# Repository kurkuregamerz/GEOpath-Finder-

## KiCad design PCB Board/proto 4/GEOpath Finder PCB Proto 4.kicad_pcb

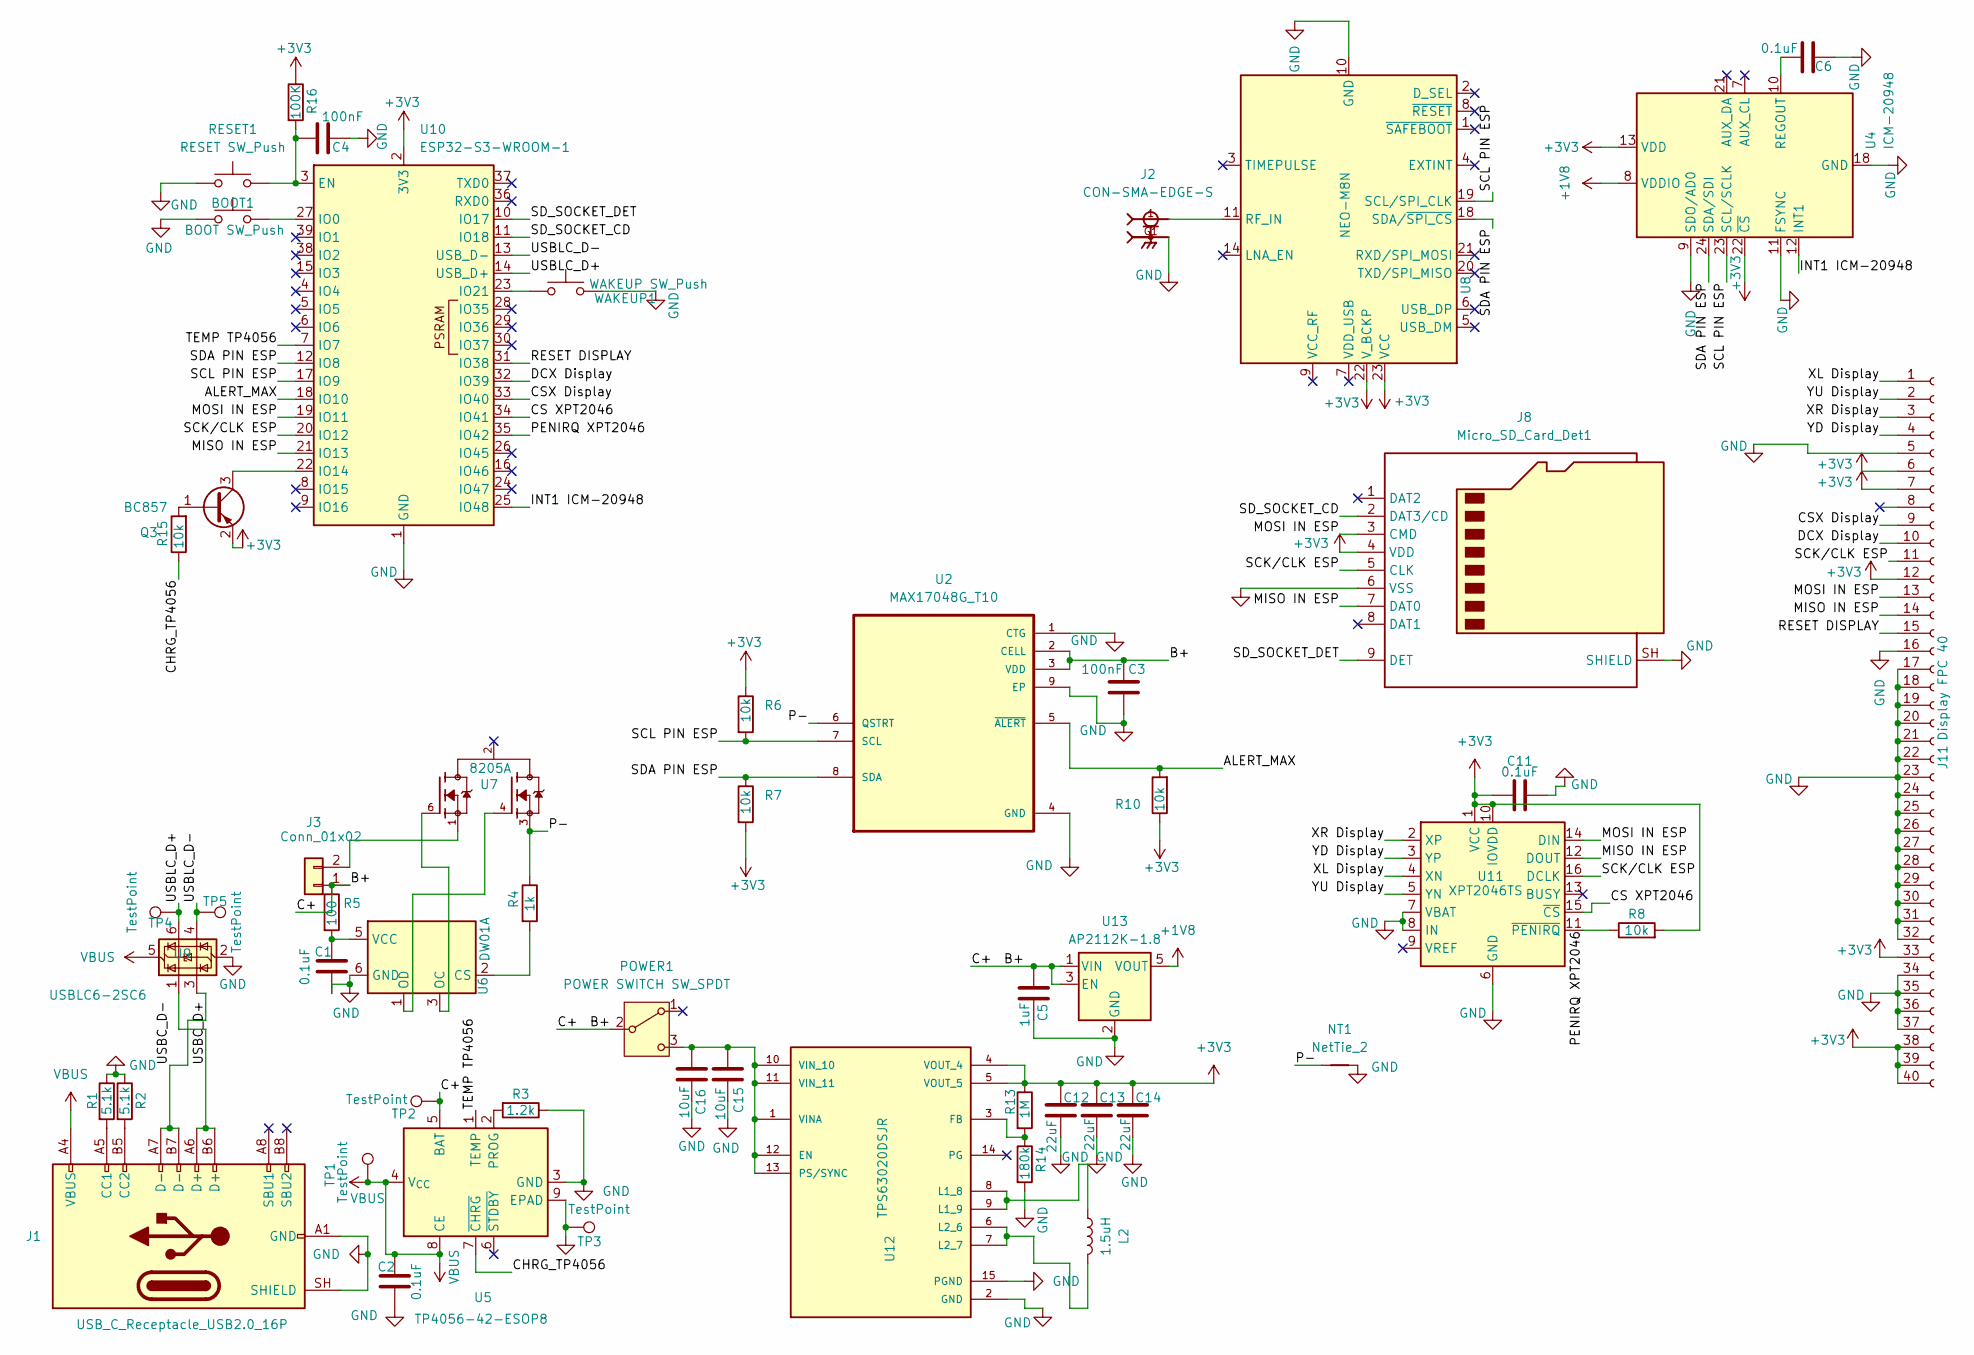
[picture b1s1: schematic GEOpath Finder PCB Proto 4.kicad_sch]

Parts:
BOOT1: BOOT SW_Push; SW_PUSH_6mm
C1, C2, C6, C11: 0.1uF; C_0201_0603Metric
C3, C4: 100nF; C_0201_0603Metric
C5: 1uF; C_0201_0603Metric
C12, C13, C14: 22uF; C_1206_3216Metric
C15, C16: 10uF; C_0603_1608Metric
J1: USB_C_Receptacle_USB2.0_16P; USB_C_Receptacle_GCT_USB4085
J2: CON-SMA-EDGE-S; RFSOLUTIONS_CON-SMA-EDGE-S; PARTREV 1
J3: Conn_01x02; JST_EH_S2B-EH_1x02_P2.50mm_Horizontal
J8: Micro_SD_Card_Det1; microSD_HC_Hirose_DM3AT-SF-PEJM5
J11: Display FPC 40; Amphenol_F32Q-1A7x1-11040_1x40-1MP_P0.5mm_Horizontal
L2: 1.5uH; L_0201_0603Metric
NT1: NetTie_2; NetTie-2_SMD_Pad0.5mm
POWER1: POWER SWITCH SW_SPDT; SW_Slide_SPDT_Angled_CK_OS102011MA1Q
Q3: BC857; SOT-23
R1, R2: 5.1k; R_0201_0603Metric
R3: 1.2k; R_0201_0603Metric
R4: 1k; R_0201_0603Metric
R5: 100; R_0201_0603Metric
R6, R7, R8, R10, R15: 10k; R_0201_0603Metric
R13: 1M; R_1206_3216Metric
R14: 180k; R_0201_0603Metric
R16: 100K; R_0201_0603Metric
RESET1: RESET SW_Push; SW_PUSH_6mm
TP1, TP2, TP3, TP4, TP5: TestPoint; TestPoint_THTPad_D1.0mm_Drill0.5mm
U2: MAX17048G_T10; SON50P200X200X80-9N; MPN MAX17048G+T10
U4: ICM-20948; InvenSense_QFN-24_3x3mm_P0.4mm
U5: TP4056-42-ESOP8; SOIC-8-1EP_3.9x4.9mm_P1.27mm_EP2.41x3.3mm_ThermalVias
U6: DW01A; SOT-23-6
U7: 8205A; SOT95P285X140-6N; PARTREV NA
U8: NEO-M8N; ublox_NEO
U9: USBLC6-2SC6; SOT-23-6
U10: ESP32-S3-WROOM-1
U11: XPT2046TS; TSSOP-16_4.4x5mm_P0.65mm
U12: TPS63020DSJR; IC_TPS63020DSJR; MPN TPS63020DSJR
U13: AP2112K-1.8; SOT-23-5
WAKEUP1: WAKEUP SW_Push; SW_Push_1P1T-MP_NO_Horizontal_Alps_SKRTLAE010

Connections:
+1V8: U4.8 (VDDIO), U13.5 (VOUT)
+3V3: C11.1, C12.1, C13.1, C14.1, J8.4 (VDD), J11.6, J11.7, J11.12, J11.33, J11.38, J11.39, J11.40, Q3.2 (E), R6.1, R7.2, R8.2, R10.1, R13.1, R16.1, U4.13 (VDD), U4.22 (~CS), U8.22 (V_BCKP), U8.23 (VCC), U10.2 (3V3), U11.1 (VCC), U11.10 (IOVDD), U12.4 (VOUT_4), U12.5 (VOUT_5)
/ALERT_MAX: R10.2, U2.5 (~ALERT), U10.18 (IO10)
/B+: C3.1, C5.1, J3.1, POWER1.2 (B), R5.1, TP2.1 (1_1), U2.2 (CELL), U2.3 (VDD), U5.5 (BAT), U13.1 (VIN), U13.3 (EN)
/CHRG_TP4056: R15.1, U5.7 (~CHRG)
/CS XPT2046: U10.34 (IO41), U11.15 (~CS)
/CSX Display: J11.9, U10.33 (IO40)
/DCX Display: J11.10, U10.32 (IO39)
/INT1 ICM-20948: U4.12 (INT1), U10.25 (IO48)
/MISO IN ESP: J8.7 (DAT0), J11.14, U10.21 (IO13), U11.12 (DOUT)
/MOSI IN ESP: J8.3 (CMD), J11.13, U10.19 (IO11), U11.14 (DIN)
/P-: NT1.1, R4.1, U2.6 (QSTRT), U7.3
/PENIRQ XPT2046: R8.1, U10.35 (IO42), U11.11 (~PENIRQ)
/RESET DISPLAY: J11.15, U10.31 (IO38)
/SCK/CLK ESP: J8.5 (CLK), J11.11, U10.20 (IO12), U11.16 (DCLK)
/SCL PIN ESP: R6.2, U2.7 (SCL), U4.23 (SCL/SCLK), U8.19 (SCL/SPI_CLK), U10.17 (IO9)
/SDA PIN ESP: R7.1, U2.8 (SDA), U4.24 (SDA/SDI), U8.18 (SDA/~SPI_CS), U10.12 (IO8)
/SD_SOCKET_CD: J8.2 (DAT3/CD), U10.11 (IO18)
/SD_SOCKET_DET: J8.9 (DET), U10.10 (IO17)
/TEMP TP4056: U5.1 (TEMP), U10.7 (IO7)
/USBC_D+: J1.A6 (D+), J1.B6 (D+), U9.1 (I/O1)
/USBC_D-: J1.A7 (D-), J1.B7 (D-), U9.3 (I/O2)
/USBLC_D+: TP4.1 (1_1), U9.6 (I/O1), U10.14 (USB_D+)
/USBLC_D-: TP5.1 (1_1), U9.4 (I/O2), U10.13 (USB_D-)
/XL Display: J11.1, U11.4 (XN)
/XR Display: J11.3, U11.2 (XP)
/YD Display: J11.4, U11.3 (YP)
/YU Display: J11.2, U11.5 (YN)
GND: BOOT1.1, C1.2, C2.2, C3.2, C4.2, C5.2, C6.2, C11.2, C12.2, C13.2, C14.2, C15.2, C16.2, J1.A1 (GND), J1.A12 (GND), J1.B1 (GND), J1.B12 (GND), J1.SH (SHIELD), J2.G1, J2.G2, J2.G3, J2.G4, J8.6 (VSS), J8.SH (SHIELD), J11.5, J11.16, J11.17, J11.18, J11.19, J11.20, J11.21, J11.22, J11.23, J11.24, J11.25, J11.26, J11.27, J11.28, J11.29, J11.30, J11.31, J11.32, J11.34, J11.35, J11.36, J11.37, NT1.2, R1.1, R2.1, R3.1, R14.2, RESET1.1, TP3.1 (1_1), U2.1 (CTG), U2.4 (GND), U2.9 (EP), U4.9 (SDO/AD0), U4.11 (FSYNC), U4.18 (GND), U4.20 (GND), U5.3 (GND), U5.9 (EPAD), U6.6 (GND), U8.10 (GND), U8.12 (GND), U8.13 (GND), U8.24 (GND), U9.2 (GND), U10.1 (GND), U10.40 (GND), U10.41 (GND), U11.6 (GND), U11.7 (VBAT), U11.8 (IN), U12.2 (GND), U12.15 (PGND), U13.2 (GND), WAKEUP1.2
unnamed: J1.A5 (CC1), R1.2
unnamed: J1.B5 (CC2), R2.2
unnamed: J3.2, U7.1
unnamed: C15.1, C16.1, POWER1.3 (C), U12.1 (VINA), U12.10 (VIN_10), U12.11 (VIN_11), U12.12 (EN), U12.13 (PS/SYNC)
unnamed: Q3.1 (B), R15.2
unnamed: Q3.3 (C), U10.22 (IO14)
unnamed: C6.1, U4.10 (REGOUT)
unnamed: R3.2, U5.2 (PROG)
unnamed: R4.2, U6.2 (CS)
unnamed: U6.3 (OC), U7.6
unnamed: U6.1 (OD), U7.4
unnamed: C1.1, R5.2, U6.5 (VCC)
unnamed: J2.1, U8.11 (RF_IN)
unnamed: C4.1, R16.2, RESET1.2, U10.3 (EN)
unnamed: BOOT1.2, U10.27 (IO0)
unnamed: U10.23 (IO21), WAKEUP1.1
unnamed: R13.2, R14.1, U12.3 (FB)
unnamed: L2.1, U12.8 (L1_8), U12.9 (L1_9)
unnamed: L2.2, U12.6 (L2_6), U12.7 (L2_7)
VBUS: C2.1, J1.A4 (VBUS), J1.A9 (VBUS), J1.B4 (VBUS), J1.B9 (VBUS), TP1.1 (1_1), U5.4 (V_{CC}), U5.8 (CE), U9.5 (VBUS)

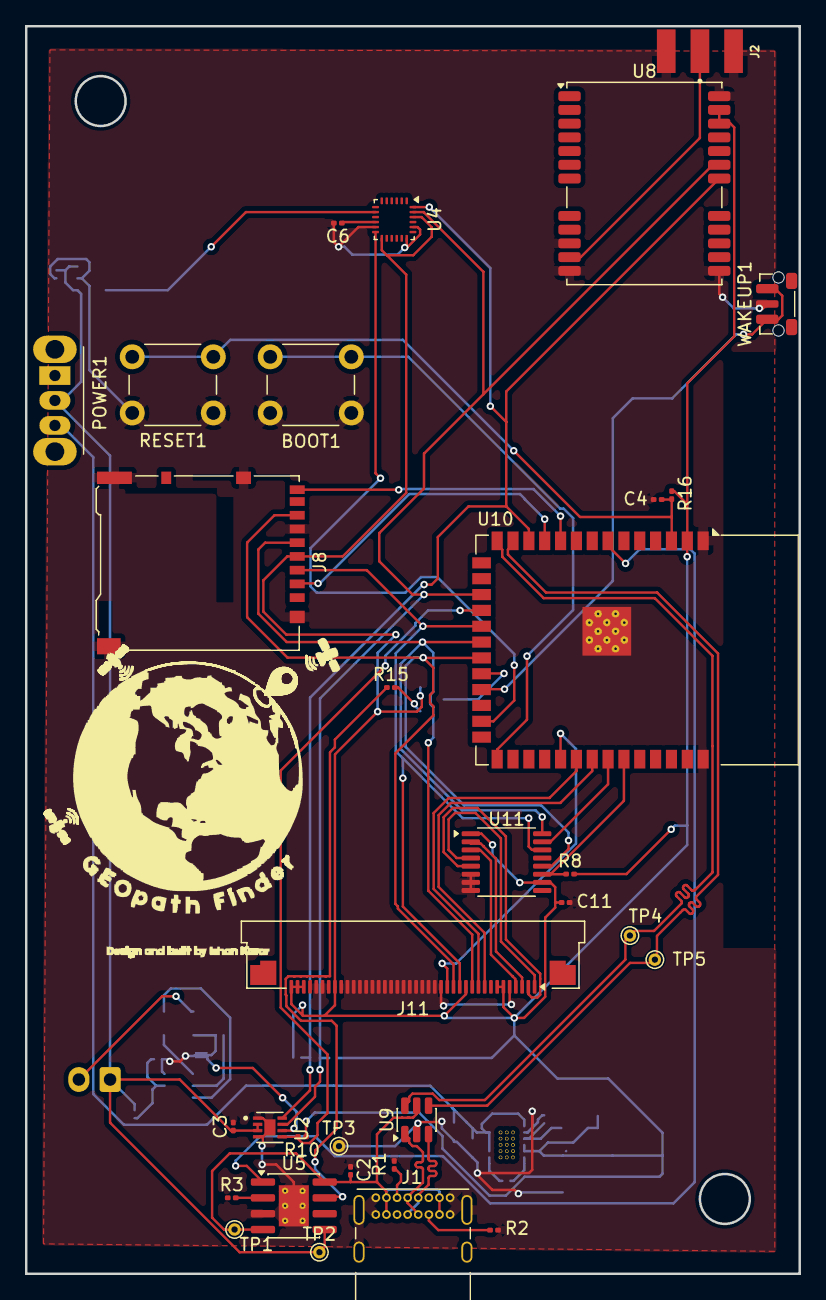
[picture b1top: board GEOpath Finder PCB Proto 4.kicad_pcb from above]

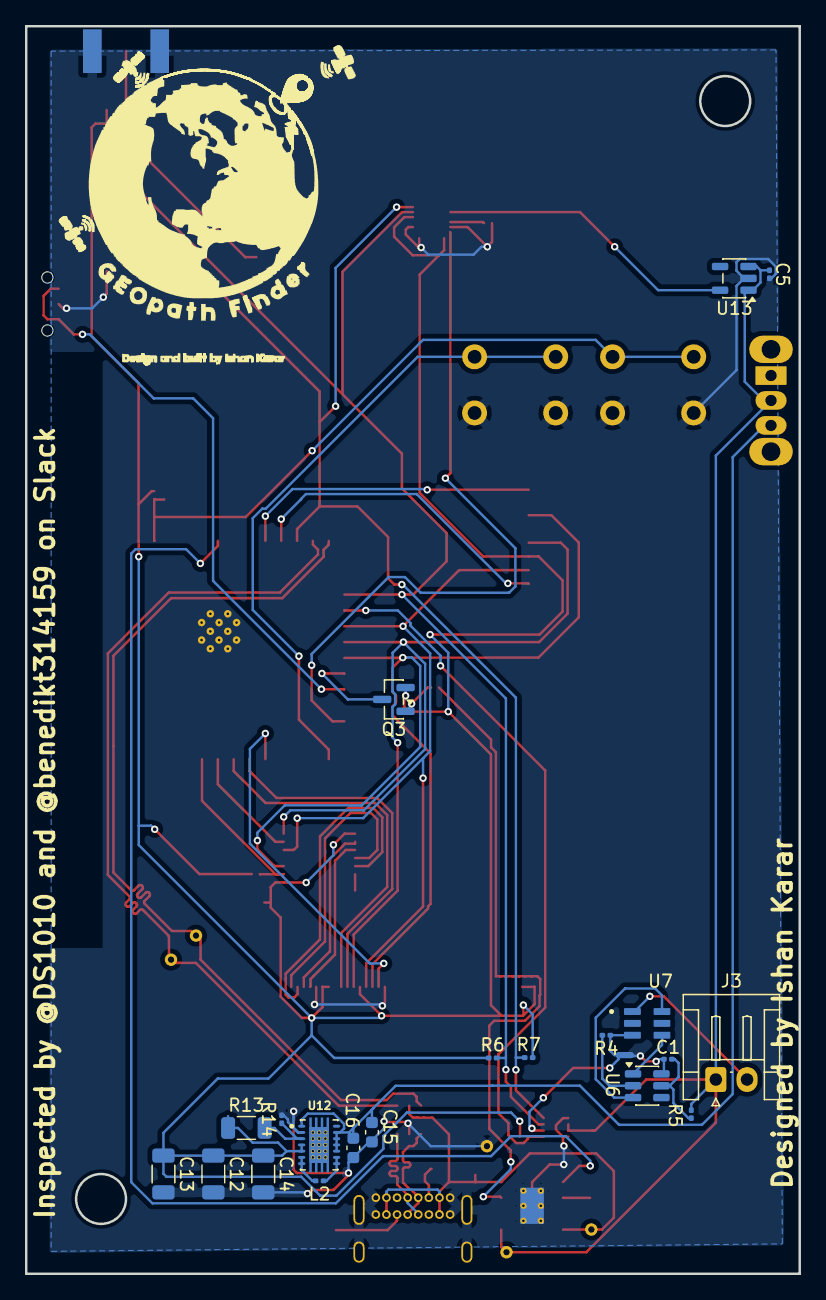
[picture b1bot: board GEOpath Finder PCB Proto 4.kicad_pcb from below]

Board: 2 copper layers, 62.0 x 100.0 mm, 53 parts (21 on the bottom side), 49 nets.

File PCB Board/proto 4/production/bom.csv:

Designator,Footprint,Quantity,Value,LCSC Part #
BOOT1,SW_PUSH_6mm,1,BOOT SW_Push,
"C1, C11, C2, C6",0201,4,0.1uF,
"C12, C13, C14",1206,3,22uF,
"C15, C16",0603,2,10uF,
"C3, C4",0201,2,100nF,
C5,0201,1,1uF,
J1,USB_C_Receptacle_GCT_USB4085,1,USB_C_Receptacle_USB2.0_16P,
J11,Amphenol_F32Q-1A7x1-11040_1x40-1MP_P0.5mm_Horizontal,1,Display FPC 40,
J2,RFSOLUTIONS_CON-SMA-EDGE-S,1,CON-SMA-EDGE-S,
J3,JST_EH_S2B-EH_1x02_P2.50mm_Horizontal,1,Conn_01x02,
J8,microSD_HC_Hirose_DM3AT-SF-PEJM5,1,Micro_SD_Card_Det1,
L2,0201,1,1.5uH,
POWER1,SW_Slide_SPDT_Angled_CK_OS102011MA1Q,1,POWER SWITCH SW_SPDT,
Q3,SOT-23,1,BC857,
"R1, R2",0201,2,5.1k,
"R10, R15, R6, R7, R8",0201,5,10k,
R13,1206,1,1M,
R14,0201,1,180k,
R16,0201,1,100K,
R3,0201,1,1.2k,
R4,0201,1,1k,
R5,0201,1,100,
RESET1,SW_PUSH_6mm,1,RESET SW_Push,
"TP1, TP2, TP3, TP4, TP5",TestPoint_THTPad_D1.0mm_Drill0.5mm,5,TestPoint,
U10,ESP32-S3-WROOM-1,1,ESP32-S3-WROOM-1,
U11,TSSOP-16_4.4x5mm_P0.65mm,1,XPT2046TS,
U12,IC_TPS63020DSJR,1,TPS63020DSJR,TPS63020DSJR
U13,SOT-23-5,1,AP2112K-1.8,
U2,SON50P200X200X80-9N,1,MAX17048G_T10,MAX17048G+T10
U4,InvenSense_QFN-24_3x3mm_P0.4mm,1,ICM-20948,
U5,SOIC-8-1EP_3.9x4.9mm_P1.27mm_EP2.41x3.3mm_ThermalVias,1,TP4056-42-ESOP8,
U6,SOT-23-6,1,DW01A,
U7,SOT95P285X140-6N,1,8205A,
U8,ublox_NEO,1,NEO-M8N,
U9,SOT-23-6,1,USBLC6-2SC6,
WAKEUP1,SW_Push_1P1T-MP_NO_Horizontal_Alps_SKRTLAE010,1,WAKEUP SW_Push,

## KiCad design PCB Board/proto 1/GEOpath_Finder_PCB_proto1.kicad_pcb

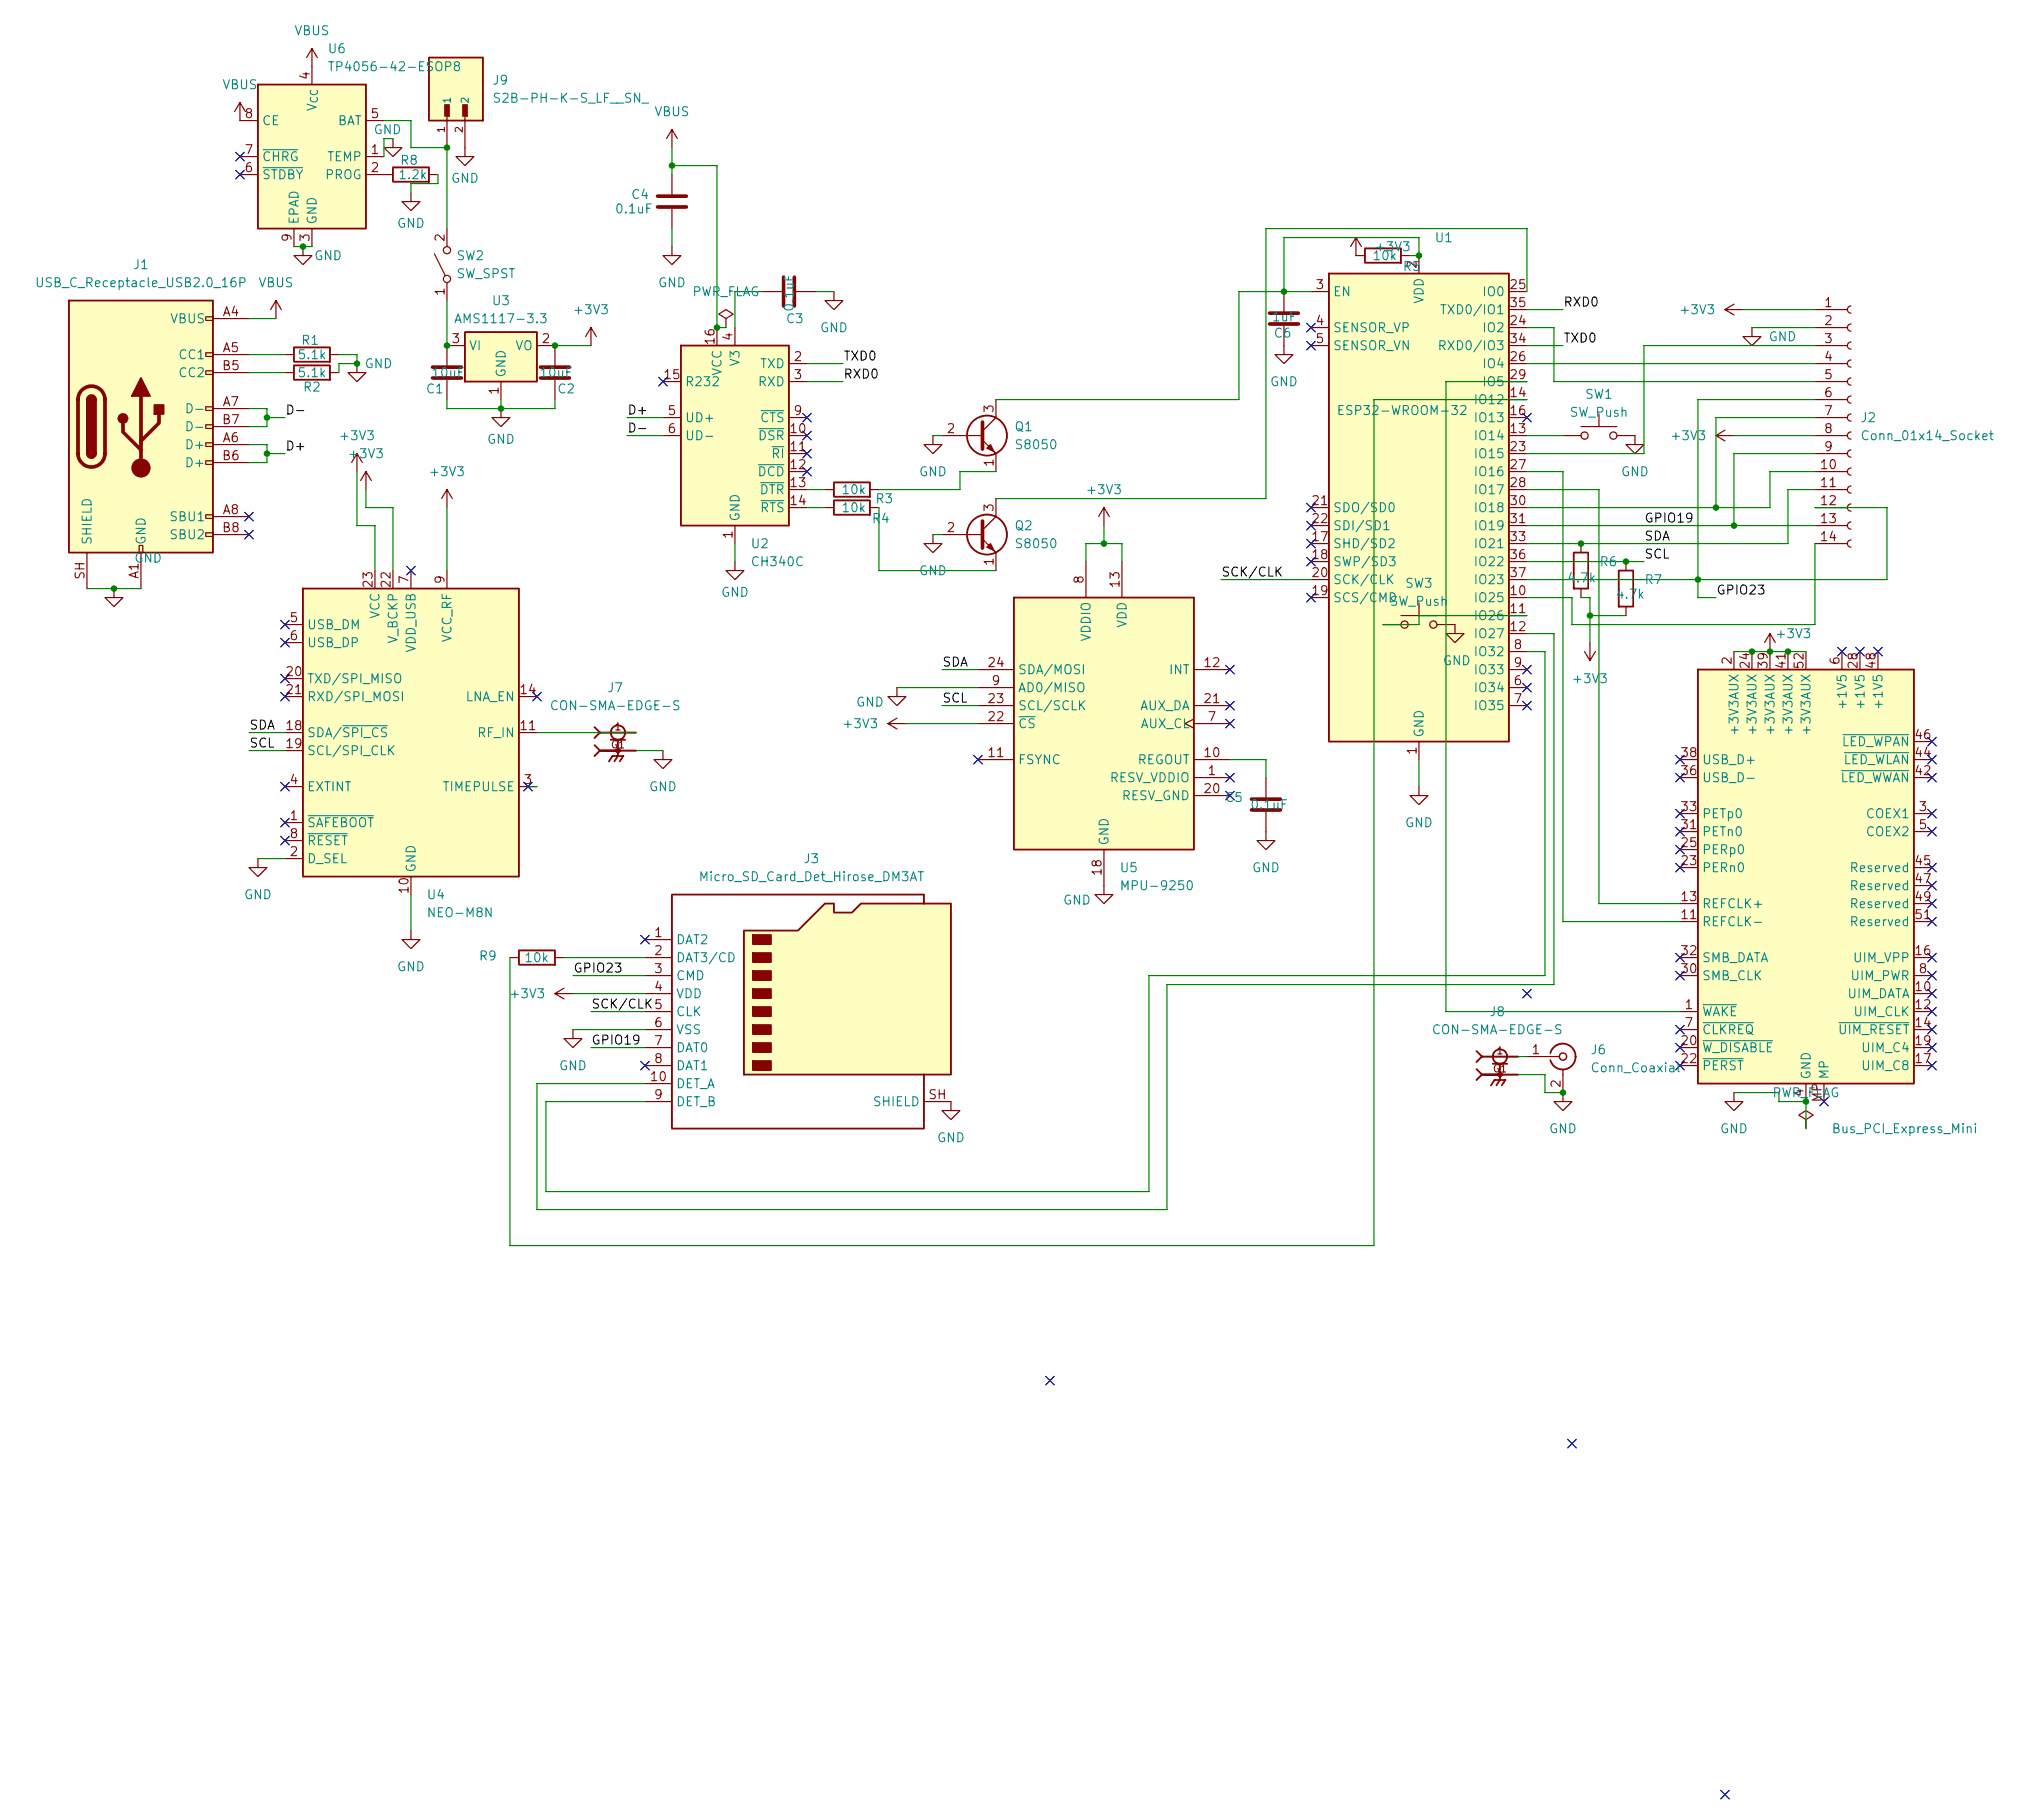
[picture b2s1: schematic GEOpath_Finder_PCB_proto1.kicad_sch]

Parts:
C1, C2: 10uF; C_0805_2012Metric
C3, C4, C5: 0.1uF; C_0603_1608Metric
C6: 1uF; C_0603_1608Metric
J1: USB_C_Receptacle_USB2.0_16P; USB_C_Receptacle_GCT_USB4085
J2: Conn_01x14_Socket; PinSocket_1x14_P2.54mm_Vertical
J3: Micro_SD_Card_Det_Hirose_DM3AT; microSD_HC_Hirose_DM3AT-SF-PEJM5
J5: Bus_PCI_Express_Mini; BUS_PCI_Express_Mini
J6: Conn_Coaxial; U.FL_Hirose_U.FL-R-SMT-1_Vertical
J7, J8: CON-SMA-EDGE-S; RFSOLUTIONS_CON-SMA-EDGE-S; PARTREV 1
J9: S2B-PH-K-S_LF__SN_; JST_S2B-PH-K-S_LF__SN_; PARTREV R0
Q1, Q2: S8050; SOT-23
R1, R2: 5.1k; R_0201_0603Metric
R3, R4, R5, R9: 10k; R_0201_0603Metric
R6, R7: 4.7k; R_0201_0603Metric
R8: 1.2k; R_0201_0603Metric
SW1, SW3: SW_Push; SW_SPST_PTS645Sx43SMTR92
SW2: SW_SPST; SW_SPDT_PCM12
U1: ESP32-WROOM-32
U2: CH340C; SOIC-16_3.9x9.9mm_P1.27mm
U3: AMS1117-3.3; SOT-223-3_TabPin2
U4: NEO-M8N; ublox_NEO
U5: MPU-9250; InvenSense_QFN-24_3x3mm_P0.4mm
U6: TP4056-42-ESOP8; SOIC-8-1EP_3.9x4.9mm_P1.27mm_EP2.41x3.3mm_ThermalVias

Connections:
/D+: J1.A6 (D+), J1.B6 (D+), U2.5 (UD+)
/D-: J1.A7 (D-), J1.B7 (D-), U2.6 (UD-)
/GPIO19: J2.9, J2.13, J3.7 (DAT0), U1.31 (IO19)
/GPIO23: J2.6, J2.12, J3.3 (CMD), U1.37 (IO23)
/RXD0: U1.35 (TXD0/IO1), U2.3 (RXD)
/SCK/CLK: J3.5 (CLK), U1.20 (SCK/CLK)
/SCL: R7.1, U1.36 (IO22), U4.19 (SCL/SPI_CLK), U5.23 (SCL/SCLK)
/SDA: J2.11, R6.1, U1.33 (IO21), U4.18 (SDA/~SPI_CS), U5.24 (SDA/MOSI)
/TXD0: U1.34 (RXD0/IO3), U2.2 (TXD)
GND: C1.2, C2.2, C3.1, C4.2, C5.2, C6.2, J1.A1 (GND), J1.A12 (GND), J1.B1 (GND), J1.B12 (GND), J1.SH (SHIELD), J2.2, J3.6 (VSS), J3.SH (SHIELD), J5.4 (GND), J5.9 (GND), J5.15 (GND), J5.18 (GND), J5.21 (GND), J5.26 (GND), J5.27 (GND), J5.29 (GND), J5.34 (GND), J5.35 (GND), J5.37 (GND), J5.40 (GND), J5.43 (GND), J5.50 (GND), J6.2 (Ext), J7.G1, J7.G2, J7.G3, J7.G4, J8.G1, J8.G2, J8.G3, J8.G4, J9.2, Q1.2 (B), Q2.2 (B), R1.2, R2.2, R8.2, SW1.2, SW3.2, U1.1 (GND), U1.15 (GND), U1.38 (GND), U1.39 (GND), U2.1 (GND), U3.1 (GND), U4.2 (D_SEL), U4.10 (GND), U4.12 (GND), U4.13 (GND), U4.24 (GND), U5.9 (AD0/MISO), U5.18 (GND), U6.1 (TEMP), U6.3 (GND), U6.9 (EPAD)
unnamed: J1.A5 (CC1), R1.1
unnamed: J1.B5 (CC2), R2.1
unnamed: J2.3, U1.23 (IO15)
unnamed: J2.4, U1.26 (IO4)
unnamed: J2.5, U1.24 (IO2)
unnamed: J2.7, J2.10, U1.30 (IO18)
unnamed: J2.14, U1.10 (IO25)
unnamed: J3.2 (DAT3/CD), R9.2
unnamed: J3.10 (DET_A), U1.12 (IO27)
unnamed: J3.9 (DET_B), U1.8 (IO32)
unnamed: J5.13 (REFCLK+), U1.28 (IO17)
unnamed: J5.11 (REFCLK-), U1.27 (IO16)
unnamed: J5.1 (~WAKE), U1.29 (IO5)
unnamed: J6.1 (In), J8.1
unnamed: Q1.1 (E), R3.2
unnamed: Q2.3 (C), U1.25 (IO0)
unnamed: Q2.1 (E), R4.2
unnamed: C1.1, SW2.1 (A), U3.3 (VI)
unnamed: J9.1, SW2.2 (B), U6.5 (BAT)
unnamed: R9.1, U1.14 (IO12)
unnamed: SW1.1, U1.13 (IO14)
unnamed: SW3.1, U1.11 (IO26)
unnamed: C3.2, U2.4 (V3)
unnamed: R3.1, U2.13 (~DTR)
unnamed: R4.1, U2.14 (~RTS)
unnamed: J7.1, U4.11 (RF_IN)
unnamed: C5.1, U5.10 (REGOUT)
unnamed: R8.1, U6.2 (PROG)
VBUS: C4.1, J1.A4 (VBUS), J1.A9 (VBUS), J1.B4 (VBUS), J1.B9 (VBUS), U2.16 (VCC), U6.4 (V_{CC}), U6.8 (CE)

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
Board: 2 copper layers, 34 parts (8 on the bottom side), 41 nets, no tracks yet.

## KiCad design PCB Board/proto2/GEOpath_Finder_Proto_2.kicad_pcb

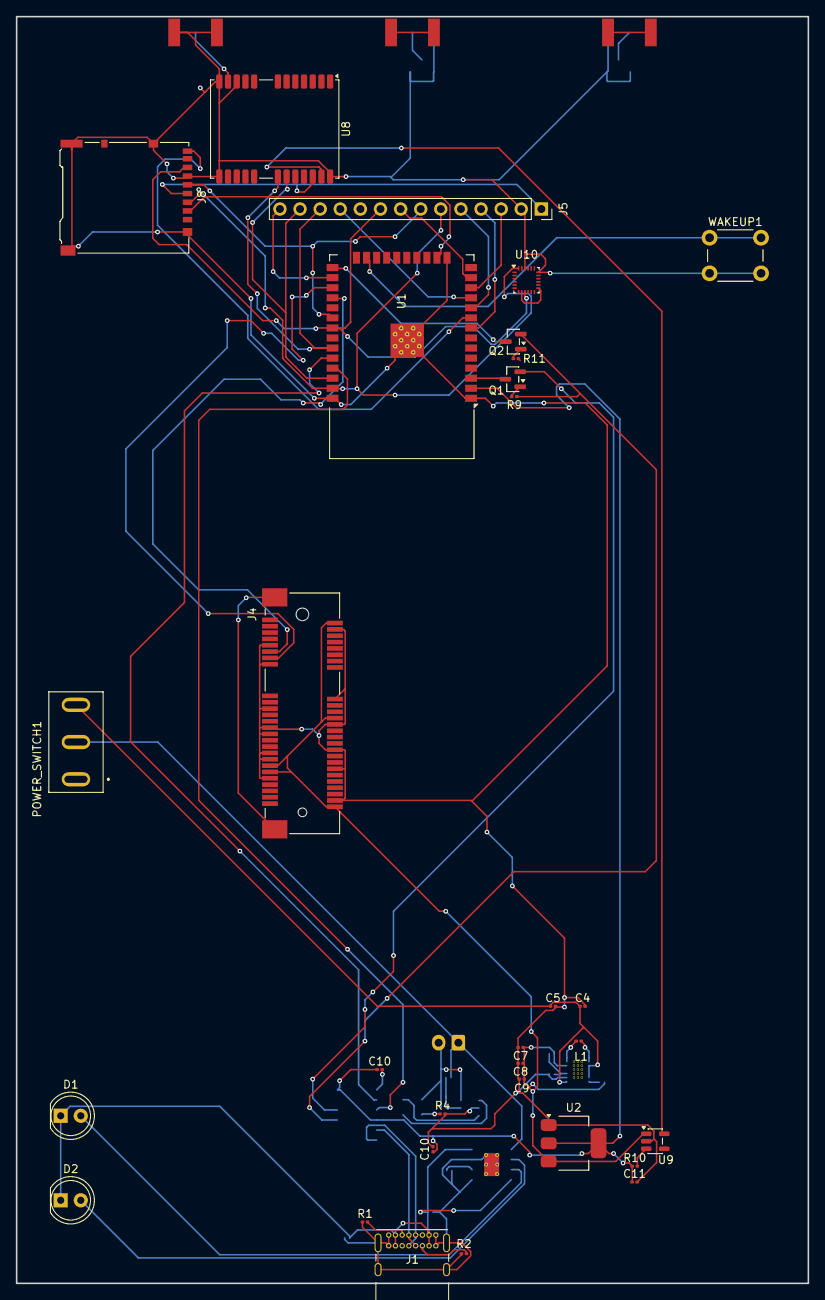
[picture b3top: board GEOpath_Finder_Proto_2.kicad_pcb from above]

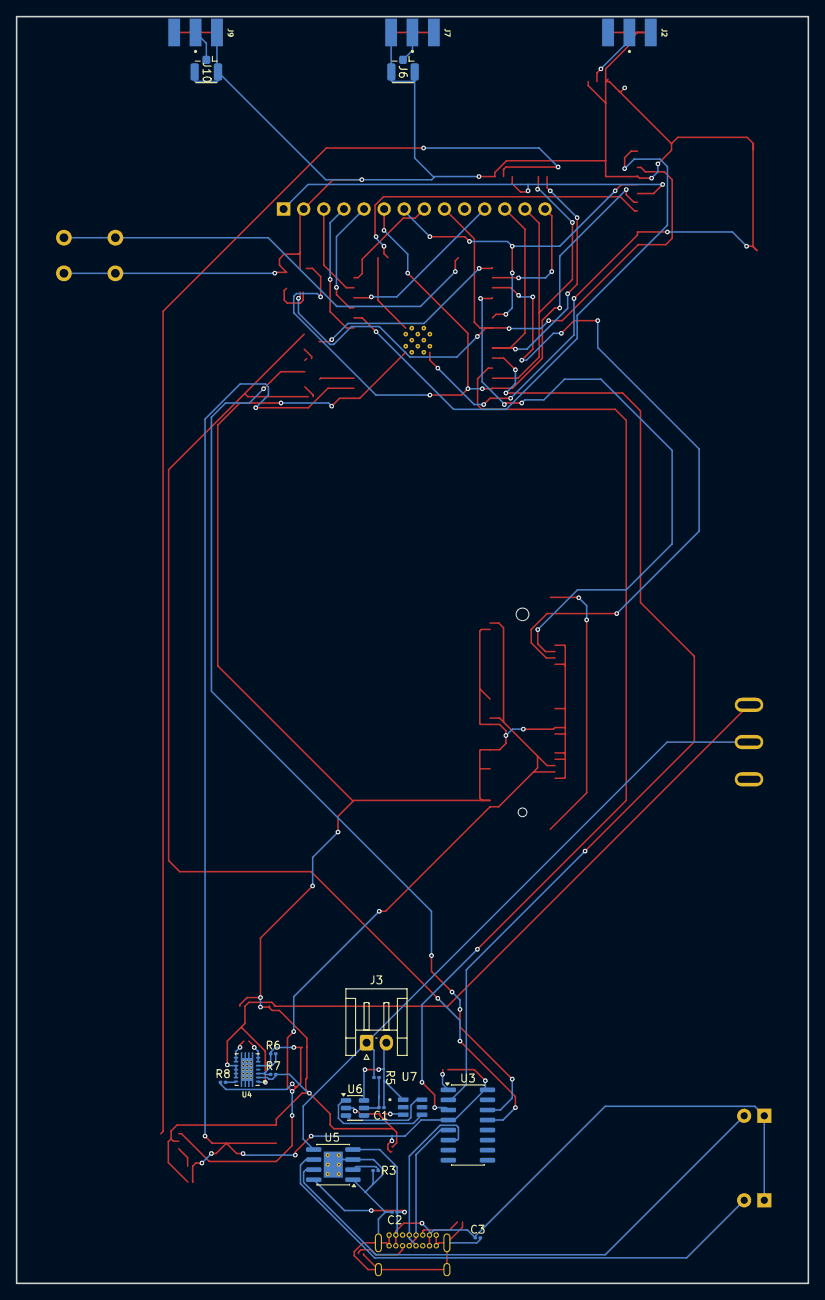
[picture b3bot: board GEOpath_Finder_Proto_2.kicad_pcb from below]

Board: 2 copper layers, 100.0 x 160.0 mm, 49 parts (19 on the bottom side), 53 nets.

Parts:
C1, C2, C3: 0.1uF; C_0201_0603Metric
C4, C5, C10, C10#2, C11: 10uF; C_0201_0603Metric
C7, C8, C9: 22uF; C_0201_0603Metric
D1, D2: LED; LED_D5.0mm
J1: USB_C_Receptacle_USB2.0_16P; USB_C_Receptacle_GCT_USB4085
J2, J7, J9: CON-SMA-EDGE-S; RFSOLUTIONS_CON-SMA-EDGE-S
J3: Conn_01x02; JST_EH_S2B-EH_1x02_P2.50mm_Horizontal
J4: Bus_PCI_Express_Mini; BUS_PCI_Express_Mini
J5: Display Connector 01x14; PinSocket_1x14_P2.54mm_Vertical
J6, J10: Conn_Coaxial; U.FL_Hirose_U.FL-R-SMT-1_Vertical
J8: Micro_SD_Card_Det1; microSD_HC_Hirose_DM3AT-SF-PEJM5
L1: 1.5uH; L_0201_0603Metric
POWER_SWITCH1: SW_SPDT; SW_100SP1T1B1M1QEH
Q1, Q2: BC817; SOT-23
R1, R2: 5.1k; R_0201_0603Metric
R3: 1.2k; R_0201_0603Metric
R4: 1k; R_0201_0603Metric
R5: 100; R_0201_0603Metric
R6: 909k; R_0201_0603Metric
R7: 100k; R_0201_0603Metric
R8: 1000k; R_0201_0603Metric
R9, R10, R11: 10k; R_0201_0603Metric
U1: ESP32-WROOM-32
U2: AMS1117-3.3; SOT-223-3_TabPin2
U3: CH340C; SOIC-16_3.9x9.9mm_P1.27mm
U4: TPS63020DSJR; IC_TPS63020DSJR
U5: TP4056-42-ESOP8; SOIC-8-1EP_3.9x4.9mm_P1.27mm_EP2.41x3.3mm_ThermalVias
U6: DW01A; SOT-23-6
U7: 8205A; SOT95P285X140-6N
U8: NEO-M8N; ublox_NEO
U9: AP2112K-1.8; SOT-23-5
U10: MPU-9250; InvenSense_QFN-24_3x3mm_P0.4mm
WAKEUP1: SW_Push; SW_PUSH_6mm

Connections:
+1V8: U8.23 (VCC), U9.5 (VOUT)
+3V3: C10.1, C10#2.1, C11.1, J5.1, J8.4 (VDD), R10.1, U1.2 (VDD), U2.2 (VO), U3.4 (V3), U3.16 (VCC), U8.22 (V_BCKP), U10.8 (VDDIO), U10.13 (VDD)
+5V: C7.1, C8.1, C9.1, J4.2 (+3V3AUX), J4.24 (+3V3AUX), J4.39 (+3V3AUX), J4.41 (+3V3AUX), J4.52 (+3V3AUX), R6.1, R8.1, U2.3 (VI), U4.5 (VOUT_5), U9.1 (VIN)
/B+: J3.1, POWER_SWITCH1.2 (B), R5.1, U5.5 (BAT)
/B-: C1.2, J3.2, U6.6 (GND), U7.1
/Backlight pin Display: J5.8, U1.13 (IO14)
/CH340C UD+: J1.A6 (D+), J1.B6 (D+), U3.5 (UD+)
/CH340C UD-: J1.A7 (D-), J1.B7 (D-), U3.6 (UD-)
/CS Display: J5.3, U1.12 (IO27)
/DTR CH340C: Q2.2 (E), R9.1, U3.13 (~DTR)
/Display DC/RS: J5.5, U1.10 (IO25)
/MISO IN ESP: J5.9, J8.7 (DAT0), U1.31 (IO19), U10.9 (AD0/MISO)
/MOSI IN ESP: J5.6, J8.3 (CMD), U1.37 (IO23), U10.24 (SDA/MOSI)
/P-: C4.2, C5.2, C7.2, C8.2, C9.2, C10.2, C10#2.2, C11.2, J2.G1, J2.G2, J2.G3, J2.G4, J4.4 (GND), J4.9 (GND), J4.15 (GND), J4.18 (GND), J4.21 (GND), J4.26 (GND), J4.27 (GND), J4.29 (GND), J4.34 (GND), J4.35 (GND), J4.37 (GND), J4.40 (GND), J4.43 (GND), J4.50 (GND), J5.2, J6.2 (Ext), J7.G1, J7.G2, J7.G3, J7.G4, J8.6 (VSS), J8.SH (SHIELD), J9.G1, J9.G2, J9.G3, J9.G4, J10.2 (Ext), R4.2, R7.2, U1.1 (GND), U1.15 (GND), U1.38 (GND), U1.39 (GND), U2.1 (GND), U3.1 (GND), U4.2 (GND), U4.15 (PGND), U6.2 (CS), U8.10 (GND), U8.12 (GND), U8.13 (GND), U8.24 (GND), U9.2 (GND), U10.18 (GND), U10.22 (~CS), WAKEUP1.2
/RST display: J5.4, U1.8 (IO32)
/RTS CH340C: Q1.2 (E), R11.2, U3.14 (~RTS)
/RXD CH340C IN: U1.35 (TXD0/IO1), U3.3 (RXD)
/RXD SWARM mPcie: J4.11 (REFCLK-), U1.28 (IO17)
/SCK/CLK ESP: J5.7, J5.10, J8.5 (CLK), U1.30 (IO18)
/SCL PIN ESP: J5.13, U1.36 (IO22), U8.19 (SCL/SPI_CLK)
/SDA PIN ESP: J5.12, U1.33 (IO21), U8.18 (SDA/~SPI_CS)
/SD_SOCKET_DET: J8.9 (DET), U1.9 (IO33)
/SD_socket_cd: J8.2 (DAT3/CD), U1.16 (IO13)
/TXD CH340C OUT: U1.34 (RXD0/IO3), U3.2 (TXD)
/TXD SWARM mPcie: J4.13 (REFCLK+), U1.27 (IO16)
/Touch Enable pin Display: J5.11, U1.11 (IO26)
/Touch interrupt Display: J5.14, U1.26 (IO4)
GND: C2.2, C3.2, J1.A1 (GND), J1.A12 (GND), J1.B1 (GND), J1.B12 (GND), J1.SH (SHIELD), R1.1, R2.1, R3.1, U5.1 (TEMP), U5.3 (GND), U5.9 (EPAD)
unnamed: D1.2 (A), U5.7 (~CHRG)
unnamed: D2.2 (A), U5.6 (~STDBY)
unnamed: J1.A5 (CC1), R1.2
unnamed: J1.B5 (CC2), R2.2
unnamed: J6.1 (In), J7.1
unnamed: J9.1, J10.1 (In)
unnamed: C4.1, C5.1, POWER_SWITCH1.3 (C), U4.1 (VINA), U4.10 (VIN_10), U4.11 (VIN_11), U4.12 (EN), U4.13 (PS/SYNC)
unnamed: Q1.1 (B), R9.2
unnamed: Q1.3 (C), U1.3 (EN)
unnamed: Q2.1 (B), R11.1
unnamed: Q2.3 (C), U1.25 (IO0)
unnamed: R4.1, U7.3
unnamed: U1.23 (IO15), WAKEUP1.1
unnamed: R6.2, R7.1, U4.3 (FB)
unnamed: L1.1, U4.8 (L1_8), U4.9 (L1_9)
unnamed: L1.2, U4.6 (L2_6), U4.7 (L2_7)
unnamed: R8.2, U4.14 (PG)
unnamed: R3.2, U5.2 (PROG)
unnamed: U6.3 (OC), U7.6
unnamed: U6.1 (OD), U7.4
unnamed: C1.1, R5.2, U6.5 (VCC)
unnamed: U7.2, U7.5
unnamed: J2.1, U8.11 (RF_IN)
unnamed: R10.2, U9.3 (EN)
VBUS: C2.1, C3.1, D1.1 (K), D2.1 (K), J1.A4 (VBUS), J1.A9 (VBUS), J1.B4 (VBUS), J1.B9 (VBUS), U5.4 (V_{CC}), U5.8 (CE)
